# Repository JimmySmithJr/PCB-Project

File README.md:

# PCB-Project
ATmega328P Dev Board

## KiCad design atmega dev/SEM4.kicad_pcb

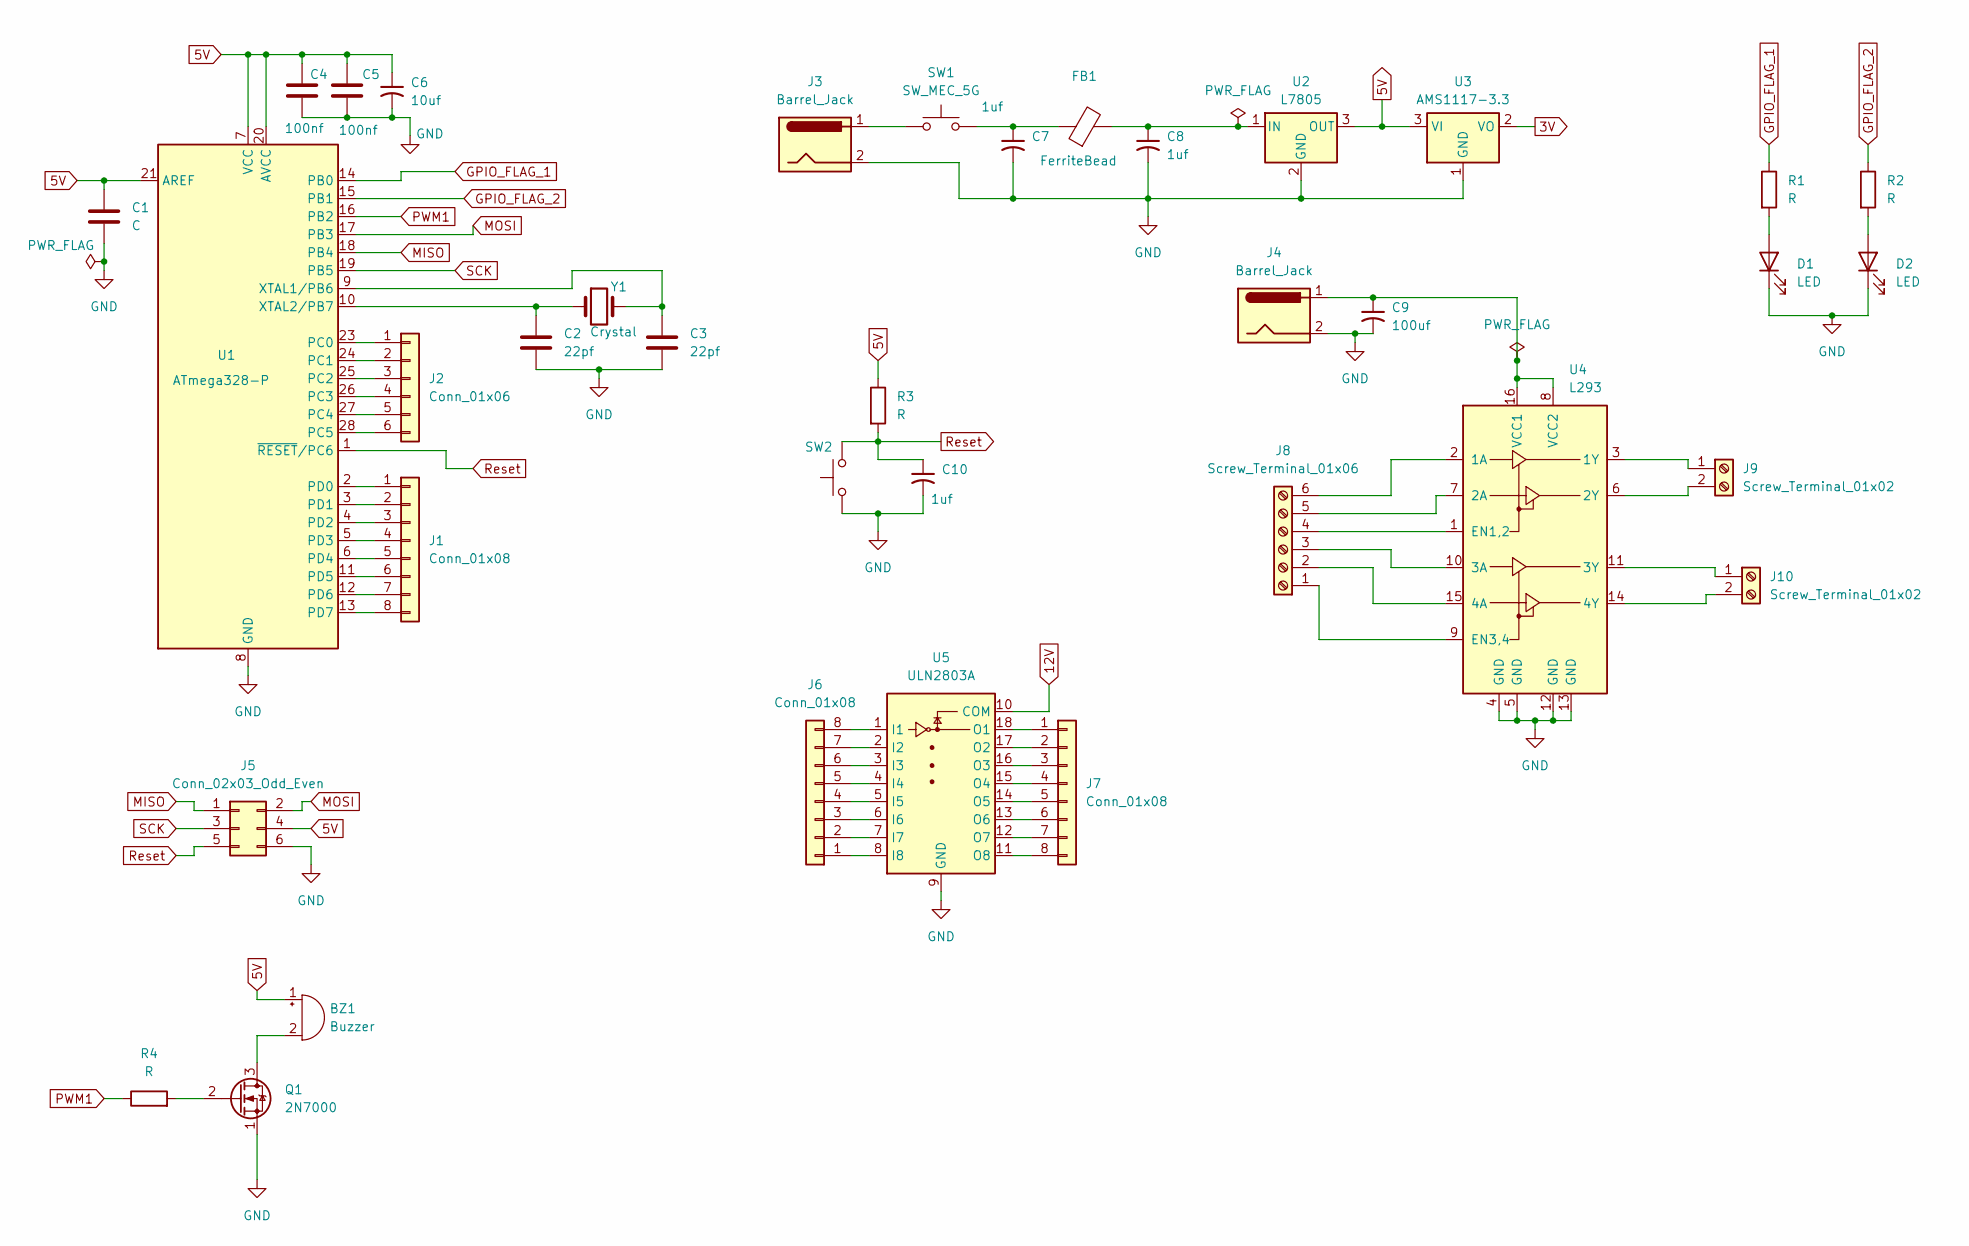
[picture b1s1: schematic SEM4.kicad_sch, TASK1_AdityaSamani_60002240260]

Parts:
BZ1: Buzzer; Buzzer_12x9.5RM7.6
C1: C; C_Disc_D3.0mm_W1.6mm_P2.50mm
C2, C3: 22pf; C_Disc_D3.0mm_W1.6mm_P2.50mm
C4, C5: 100nf; C_Disc_D3.0mm_W1.6mm_P2.50mm
C6: 10uf; C_Disc_D3.0mm_W1.6mm_P2.50mm
C7, C8, C10: 1uf; C_Disc_D3.0mm_W1.6mm_P2.50mm
C9: 100uf; C_Disc_D3.0mm_W1.6mm_P2.50mm
D1, D2: LED; LED_D2.0mm_W4.0mm_H2.8mm_FlatTop
FB1: FerriteBead; L_Radial_D6.0mm_P4.00mm
J1, J6, J7: Conn_01x08; JST_EH_B8B-EH-A_1x08_P2.50mm_Vertical
J2: Conn_01x06; Hirose_DF57H-6P-1.2V_1x06_P1.2mm_Socket
J3, J4: Barrel_Jack; BarrelJack_SwitchcraftConxall_RAPC10U_Horizontal
J5: Conn_02x03_Odd_Even; Tag-Connect_TC2030-IDC-FP_2x03_P1.27mm_Vertical
J8: Screw_Terminal_01x06; TerminalBlock_MaiXu_MX126-5.0-06P_1x06_P5.00mm
J9, J10: Screw_Terminal_01x02; TerminalBlock_MaiXu_MX126-5.0-02P_1x02_P5.00mm
Q1: 2N7000; TO-92_Inline
R1, R2, R3, R4: R; R_Axial_DIN0207_L6.3mm_D2.5mm_P7.62mm_Horizontal
SW1, SW2: SW_MEC_5G; SW_MEC_5GSH9
U1: ATmega328-P; DIP-28_W7.62mm
U2: L7805; TO-220-3_Horizontal_TabDown
U3: AMS1117-3.3; SOT-223-3_TabPin2
U4: L293; DIP-16_W7.62mm
U5: ULN2803A; DIP-18_W7.62mm
Y1: Crystal; Crystal_AT310_D3.0mm_L10.0mm_Horizontal

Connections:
3V: U3.2 (VO)
5V: BZ1.1 (+), C1.1, C4.1, C5.1, C6.1, J5.4, R3.1, U1.7 (VCC), U1.20 (AVCC), U1.21 (AREF), U2.3 (OUT), U3.3 (VI)
12V: U5.10 (COM)
GND: C1.2, C2.2, C3.2, C4.2, C5.2, C6.2, C7.2, C8.2, C9.2, C10.2, D1.1 (K), D2.1 (K), J3.2, J4.2, J5.6, Q1.1 (S), SW2.1 (A), SW2.2 (A), U1.8 (GND), U1.22 (GND), U2.2 (GND), U3.1 (GND), U4.4 (GND), U4.5 (GND), U4.12 (GND), U4.13 (GND), U5.9 (GND)
GPIO_FLAG_1: R1.1, U1.14 (PB0)
GPIO_FLAG_2: R2.1, U1.15 (PB1)
MISO: J5.1, U1.18 (PB4)
MOSI: J5.2, U1.17 (PB3)
unnamed: BZ1.2 (-), Q1.3 (D)
unnamed: C7.1, FB1.1, SW1.3 (B), SW1.4 (B)
unnamed: D1.2 (A), R1.2
unnamed: D2.2 (A), R2.2
unnamed: J1.1, U1.2 (PD0)
unnamed: J1.2, U1.3 (PD1)
unnamed: J1.3, U1.4 (PD2)
unnamed: J1.4, U1.5 (PD3)
unnamed: J1.5, U1.6 (PD4)
unnamed: J1.6, U1.11 (PD5)
unnamed: J1.7, U1.12 (PD6)
unnamed: J1.8, U1.13 (PD7)
unnamed: J2.1, U1.23 (PC0)
unnamed: J2.2, U1.24 (PC1)
unnamed: J2.3, U1.25 (PC2)
unnamed: J2.4, U1.26 (PC3)
unnamed: J2.5, U1.27 (PC4)
unnamed: J2.6, U1.28 (PC5)
unnamed: J3.1, SW1.1 (A), SW1.2 (A)
unnamed: J6.1, U5.8 (I8)
unnamed: J6.2, U5.7 (I7)
unnamed: J6.3, U5.6 (I6)
unnamed: J6.4, U5.5 (I5)
unnamed: J6.5, U5.4 (I4)
unnamed: J6.6, U5.3 (I3)
unnamed: J6.7, U5.2 (I2)
unnamed: J6.8, U5.1 (I1)
unnamed: J7.1, U5.18 (O1)
unnamed: J7.2, U5.17 (O2)
unnamed: J7.3, U5.16 (O3)
unnamed: J7.4, U5.15 (O4)
unnamed: J7.5, U5.14 (O5)
unnamed: J7.6, U5.13 (O6)
unnamed: J7.7, U5.12 (O7)
unnamed: J7.8, U5.11 (O8)
unnamed: J8.1, U4.9 (EN3,4)
unnamed: J8.2, U4.15 (4A)
unnamed: J8.3, U4.10 (3A)
unnamed: J8.4, U4.1 (EN1,2)
unnamed: J8.5, U4.7 (2A)
unnamed: J8.6, U4.2 (1A)
unnamed: J9.1, U4.3 (1Y)
unnamed: J9.2, U4.6 (2Y)
unnamed: J10.1, U4.11 (3Y)
unnamed: J10.2, U4.14 (4Y)
unnamed: Q1.2 (G), R4.2
unnamed: C3.1, U1.9 (XTAL1/PB6), Y1.2
unnamed: C2.1, U1.10 (XTAL2/PB7), Y1.1
unnamed: C8.1, FB1.2, U2.1 (IN)
unnamed: C9.1, J4.1, U4.8 (VCC2), U4.16 (VCC1)
PWM1: R4.1, U1.16 (PB2)
Reset: C10.1, J5.5, R3.2, SW2.3 (B), SW2.4 (B), U1.1 (~RESET/PC6)
SCK: J5.3, U1.19 (PB5)

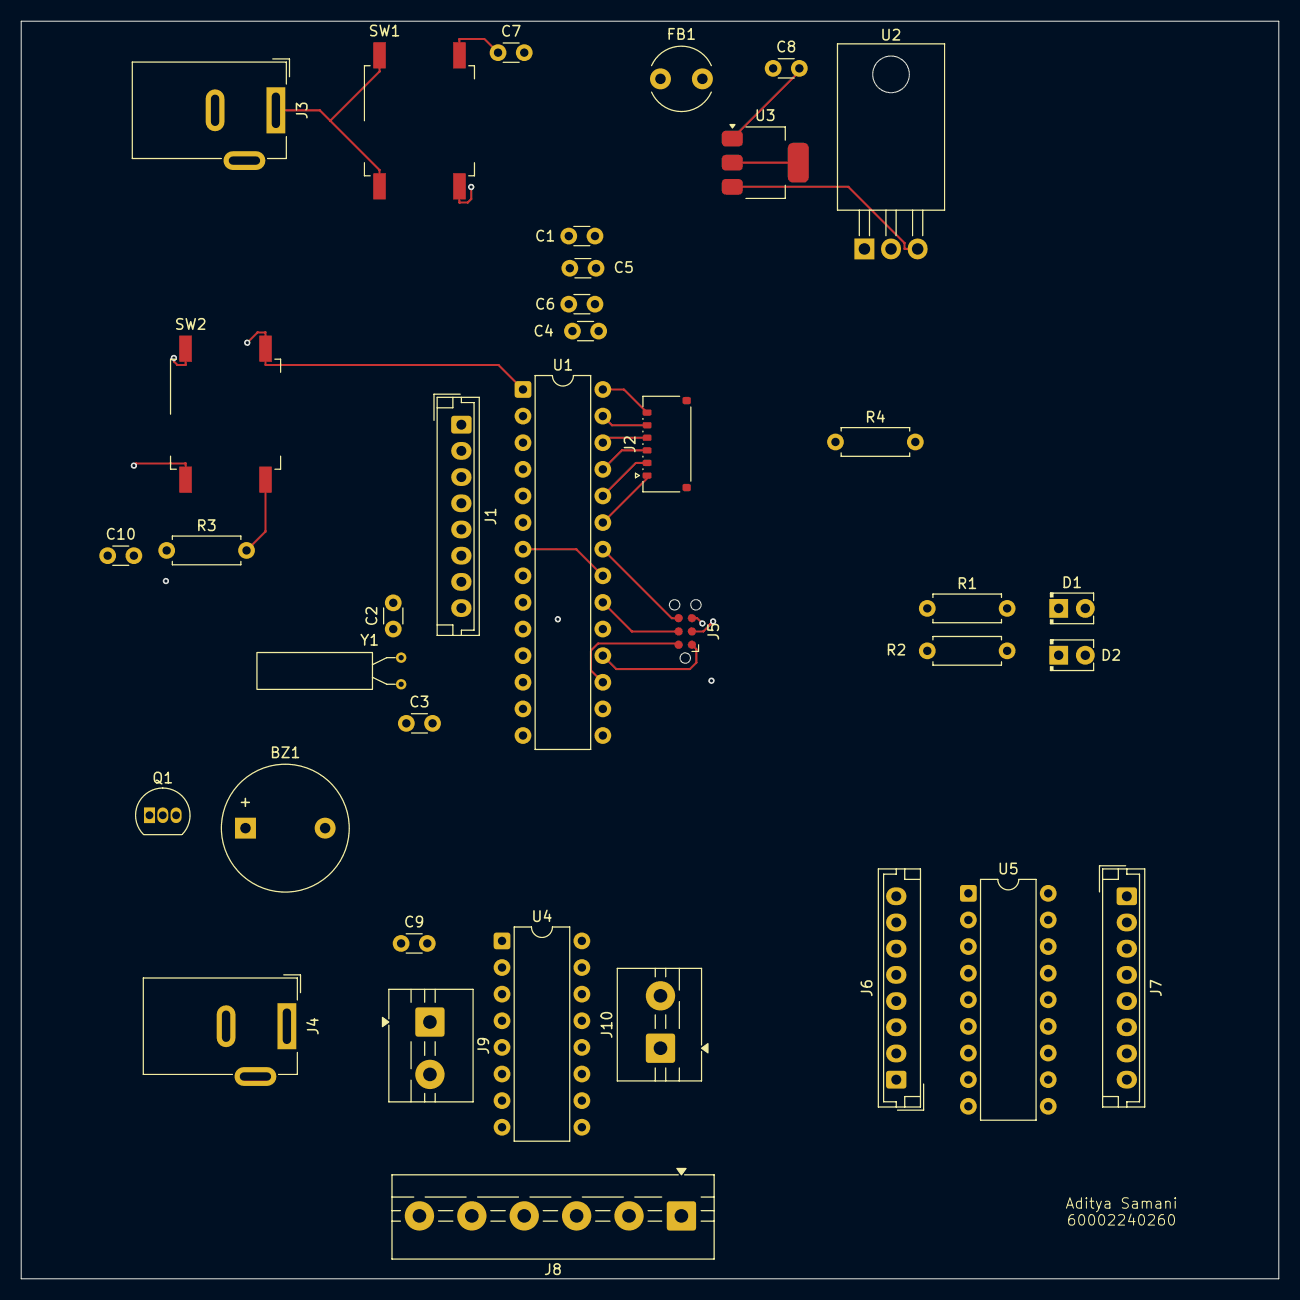
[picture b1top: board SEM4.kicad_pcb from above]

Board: 4 copper layers, 120.0 x 120.0 mm, 37 parts (0 on the bottom side), 59 nets.
